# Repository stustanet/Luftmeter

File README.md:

# Luftmeter
V1

* [test software](testfirmware/)
* [PCB](PCB/)

## ESP32
braaaaaaain...

## Sensors
* SCD30: CO2, rH, T
* HDC2080: rH, T
* MS563702BA03-50: barometer
* ...

## Interfaces
* USB-Interface: CP2102 - TTY over USB (CP210x driver)
* internal extension headers (SPI (for SDcard), I2C, )
* external expansion  (RJ45: 3V3, 5V, I2C)

## Misc
* Fan control: direct power PWM (5V, GND switched) or standard 4-pin PC-fan header
* RGB-LEDs (what else)

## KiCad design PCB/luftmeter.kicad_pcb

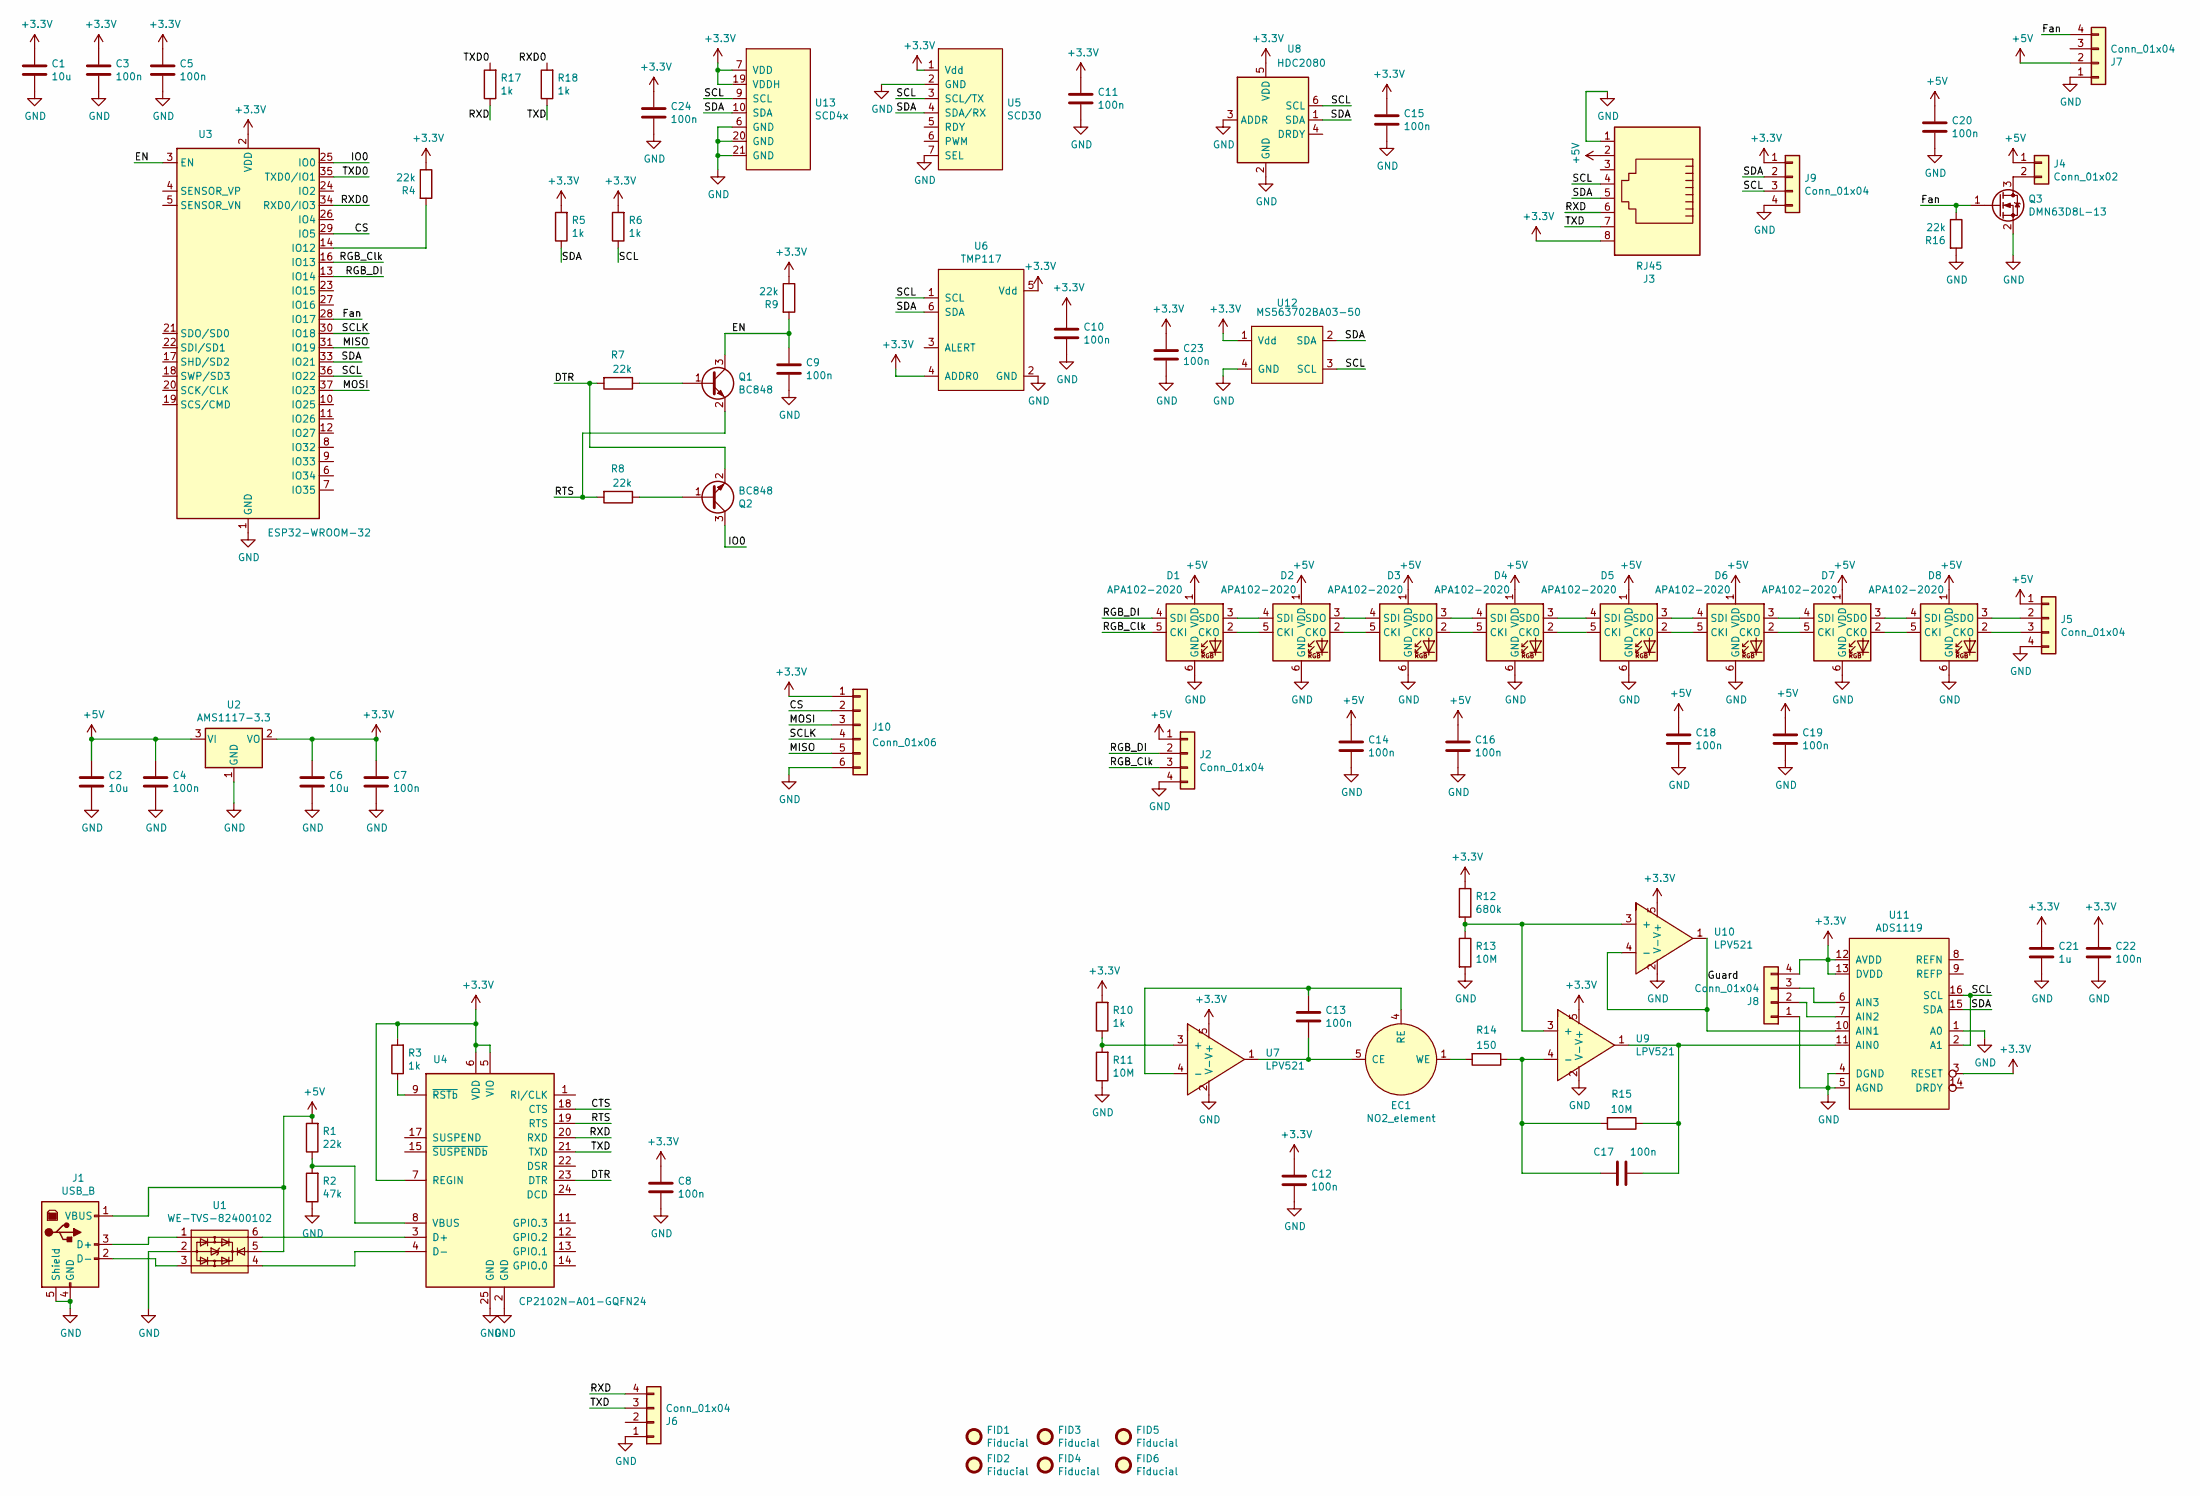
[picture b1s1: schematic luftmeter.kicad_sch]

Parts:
C1, C2, C6: 10u; C_0603_1608Metric_Pad1.08x0.95mm_HandSolder
C3, C4, C5, C7, C8, C9, C10, C11, C12, C13, C14, C15, C16, C17, C18, C19, C20, C22, C23, C24: 100n; C_0603_1608Metric_Pad1.08x0.95mm_HandSolder
C21: 1u; C_0603_1608Metric_Pad1.08x0.95mm_HandSolder
D1, D2, D3, D4, D5, D6, D7, D8: APA102-2020; LED-APA102-2020
EC1: NO2_element; SPEC_sensor_THT
FID1, FID2, FID3, FID4, FID5, FID6: Fiducial; Fiducial_1mm_Mask2mm
J1: USB_B; USB_B_Lumberg_2411_02_Horizontal; mouser 710-61400416121
J2, J5, J6, J7, J8, J9: Conn_01x04; PinHeader_1x04_P2.54mm_Vertical
J3: RJ45; RJ45_Amphenol_54602-x08_Horizontal; mouser 490-CRJ021-3-TH
J4: Conn_01x02; PinHeader_1x02_P2.54mm_Vertical
J10: Conn_01x06; PinSocket_1x06_P2.54mm_Vertical
Q1, Q2: BC848; SOT-23_Handsoldering
Q3: DMN63D8L-13; SOT-23_Handsoldering
R1, R4, R7, R8, R9, R16: 22k; R_0603_1608Metric_Pad0.98x0.95mm_HandSolder
R2: 47k; R_0603_1608Metric_Pad0.98x0.95mm_HandSolder
R3, R5, R6, R10, R17, R18: 1k; R_0603_1608Metric_Pad0.98x0.95mm_HandSolder
R11, R13, R15: 10M; R_0603_1608Metric_Pad0.98x0.95mm_HandSolder
R12: 680k; R_0603_1608Metric_Pad0.98x0.95mm_HandSolder
R14: 150; R_0603_1608Metric_Pad0.98x0.95mm_HandSolder
U1: WE-TVS-82400102; SOT-23-6
U2: AMS1117-3.3; SOT-223-3_TabPin2
U3: ESP32-WROOM-32
U4: CP2102N-A01-GQFN24; QFN-24-1EP_4x4mm_P0.5mm_EP2.6x2.6mm
U5: SCD30; SCD30_header
U6: TMP117; WSON-6-1EP_2x2mm_P0.65mm_EP1x1.6mm
U7, U9, U10: LPV521; TSOT-23-5_HandSoldering
U8: HDC2080; Texas_PWSON-N6
U11: ADS1119; TSSOP-16_4.4x5mm_P0.65mm
U12: MS563702BA03-50; TE_Baro_pres4
U13: SCD4x; QFN-20_EP_10.1x10.1_Pitch1.25mm

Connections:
+3V3: C1.1, C3.1, C5.1, C6.1, C7.1, C8.1, C10.1, C11.1, C12.1, C15.1, C21.1, C22.1, C23.1, C24.1, J3.8, J8.4, J9.1, J10.1, R3.2, R4.1, R5.2, R6.2, R9.1, R10.2, R12.1, U2.2 (VO), U3.2 (VDD), U4.5 (VIO), U4.6 (VDD), U4.7 (REGIN), U5.1 (Vdd), U6.4 (ADDR0), U6.5 (Vdd), U7.5 (V+), U8.5 (VDD), U9.5 (V+), U10.5 (V+), U11.3 (RESET), U11.12 (AVDD), U11.13 (DVDD), U12.1 (Vdd), U13.7 (VDD), U13.19 (VDDH)
+5V: C2.1, C4.1, C14.1, C16.1, C18.1, C19.1, C20.1, D1.1 (VDD), D2.1 (VDD), D3.1 (VDD), D4.1 (VDD), D5.1 (VDD), D6.1 (VDD), D7.1 (VDD), D8.1 (VDD), J1.1 (VBUS), J2.1, J3.2, J4.1, J5.1, J7.2, R1.2, U1.5, U2.3 (VI)
/CS: J10.2, U3.29 (IO5)
/CTS: U4.18 (CTS)
/DTR: Q2.2 (E), R7.2, U4.23 (DTR)
/EN: C9.1, Q1.3 (C), R9.2, U3.3 (EN)
/Fan: J7.4, Q3.1 (G), R16.1, U3.28 (IO17)
/Guard: U10.1, U10.4 (-), U11.10 (AIN1)
/IO0: Q2.3 (C), U3.25 (IO0)
/MISO: J10.5, U3.31 (IO19)
/MOSI: J10.3, U3.37 (IO23)
/RGB_Clk: D1.5 (CKI), J2.3, U3.16 (IO13)
/RGB_DI: D1.4 (SDI), J2.2, U3.13 (IO14)
/RTS: Q1.2 (E), R8.2, U4.19 (RTS)
/RXD: J3.6, J6.4, R17.1, U4.20 (RXD)
/RXD0: R18.2, U3.34 (RXD0/IO3)
/SCL: J3.4, J9.3, R6.1, U3.36 (IO22), U5.3 (SCL/TX), U6.1 (SCL), U8.6 (SCL), U11.2 (A1), U11.16 (SCL), U12.3 (SCL), U13.9 (SCL)
/SCLK: J10.4, U3.30 (IO18)
/SDA: J3.5, J9.2, R5.1, U3.33 (IO21), U5.4 (SDA/RX), U6.6 (SDA), U8.1 (SDA), U11.15 (SDA), U12.2 (SDA), U13.10 (SDA)
/TXD: J3.7, J6.3, R18.1, U4.21 (TXD)
/TXD0: R17.2, U3.35 (TXD0/IO1)
GND: C1.2, C2.2, C3.2, C4.2, C5.2, C6.2, C7.2, C8.2, C9.2, C10.2, C11.2, C12.2, C14.2, C15.2, C16.2, C18.2, C19.2, C20.2, C21.2, C22.2, C23.2, C24.2, D1.6 (GND), D2.6 (GND), D3.6 (GND), D4.6 (GND), D5.6 (GND), D6.6 (GND), D7.6 (GND), D8.6 (GND), J1.4 (GND), J1.5 (Shield), J2.4, J3.1, J5.4, J6.1, J7.1, J8.1, J9.4, J10.6, Q3.2 (S), R2.1, R11.1, R13.2, R16.2, U1.2, U2.1 (GND), U3.1 (GND), U3.15 (GND), U3.38 (GND), U3.39 (GND), U4.2 (GND), U4.25 (GND), U5.2 (GND), U5.7 (SEL), U6.2 (GND), U7.2 (V-), U8.2 (GND), U8.3 (ADDR), U9.2 (V-), U10.2 (V-), U11.1 (A0), U11.4 (DGND), U11.5 (AGND), U12.4 (GND), U13.6 (GND), U13.20 (GND), U13.21 (GND)
unnamed: C13.1, EC1.4 (RE), U7.4 (-)
unnamed: C13.2, EC1.5 (CE), U7.1
unnamed: C17.1, R14.1, R15.2, U9.4 (-)
unnamed: C17.2, R15.1, U9.1, U11.11 (AIN0)
unnamed: D1.2 (CKO), D2.5 (CKI)
unnamed: D1.3 (SDO), D2.4 (SDI)
unnamed: D2.2 (CKO), D3.5 (CKI)
unnamed: D2.3 (SDO), D3.4 (SDI)
unnamed: D3.2 (CKO), D4.5 (CKI)
unnamed: D3.3 (SDO), D4.4 (SDI)
unnamed: D4.2 (CKO), D5.5 (CKI)
unnamed: D4.3 (SDO), D5.4 (SDI)
unnamed: D5.2 (CKO), D6.5 (CKI)
unnamed: D5.3 (SDO), D6.4 (SDI)
unnamed: D6.2 (CKO), D7.5 (CKI)
unnamed: D6.3 (SDO), D7.4 (SDI)
unnamed: D7.2 (CKO), D8.5 (CKI)
unnamed: D7.3 (SDO), D8.4 (SDI)
unnamed: D8.2 (CKO), J5.3
unnamed: D8.3 (SDO), J5.2
unnamed: EC1.1 (WE), R14.2
unnamed: J1.2 (D-), U1.3
unnamed: J1.3 (D+), U1.1
unnamed: J4.2, Q3.3 (D)
unnamed: J8.2, U11.7 (AIN2)
unnamed: J8.3, U11.6 (AIN3)
unnamed: Q1.1 (B), R7.1
unnamed: Q2.1 (B), R8.1
unnamed: R1.1, R2.2, U4.8 (VBUS)
unnamed: R3.1, U4.9 (~RSTb)
unnamed: R4.2, U3.14 (IO12)
unnamed: R10.1, R11.2, U7.3 (+)
unnamed: R12.2, R13.1, U9.3 (+), U10.3 (+)
unnamed: U1.4, U4.4 (D-)
unnamed: U1.6, U4.3 (D+)

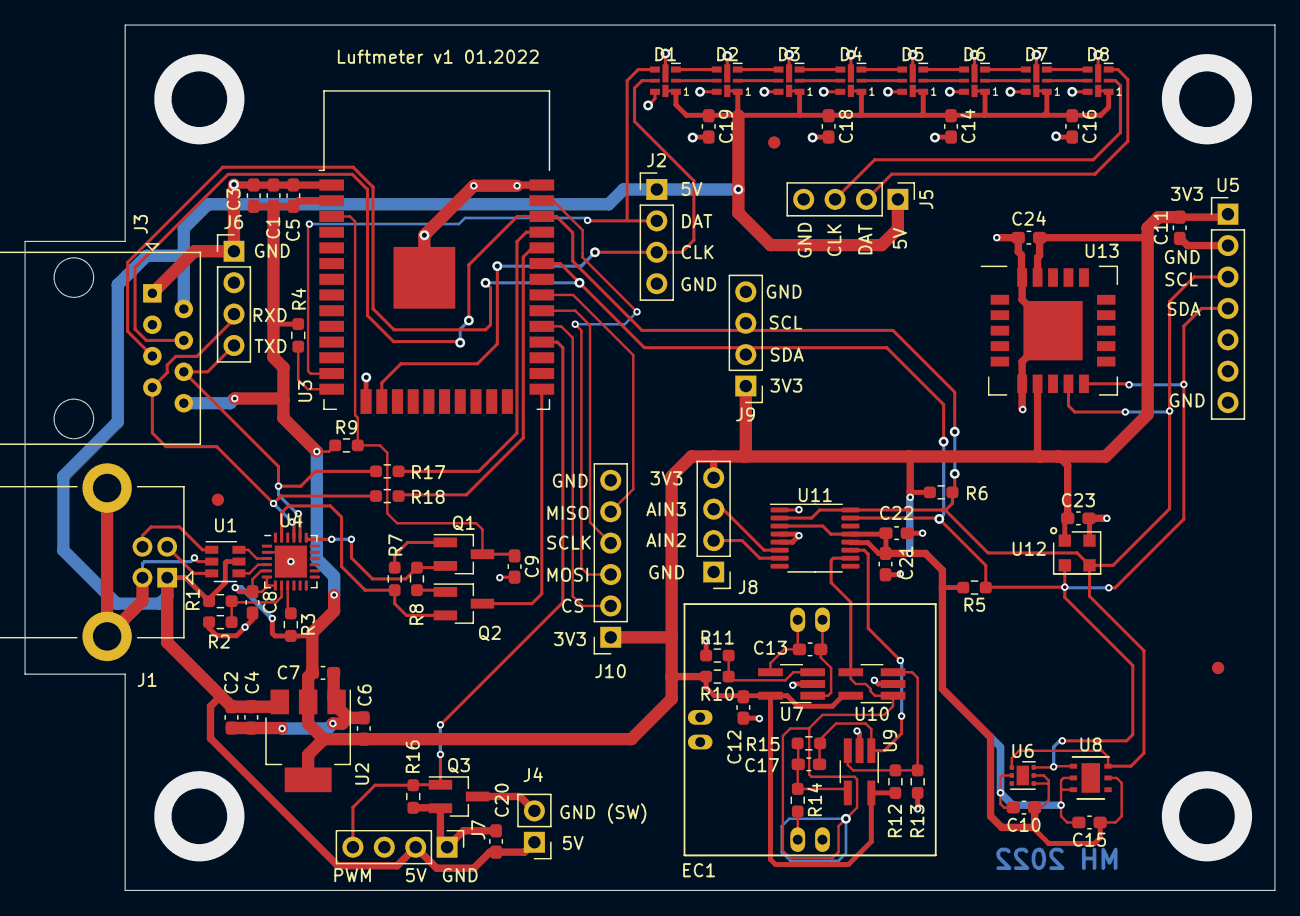
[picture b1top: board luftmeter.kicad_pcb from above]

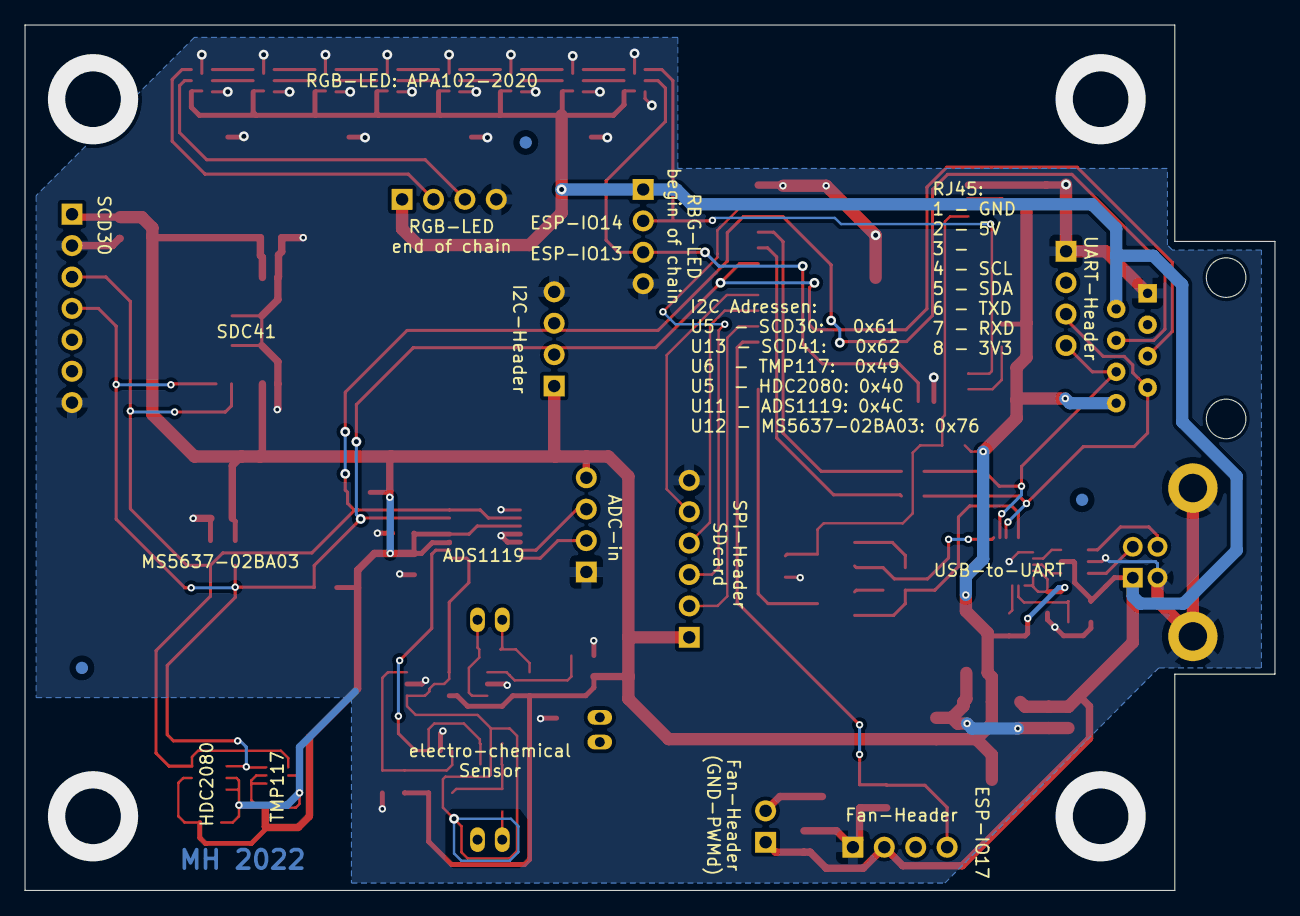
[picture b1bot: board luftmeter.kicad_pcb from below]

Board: 2 copper layers, 101.1 x 70.0 mm, 83 parts (3 on the bottom side), 56 nets.

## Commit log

2022-04-28 fix readme
2022-05-16 add SDcard, add timer, fix ads1119 bug
